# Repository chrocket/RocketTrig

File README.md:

# RocketTrig
A camera controller for photographing high poweed model rockets

This is a camera controller. Each "node" contains outputs to control one or two cameras.  Camera nodes can communicate to each others over an RF link. Two nodes make up a system, say one at the flight line and one up close to the rocket. Liftoffs can be triggered by a variety of sensors to detect lift-off, or manually via a foot switch.

Schematic, BOM, JLBPCB files and firmware are all included.
Note:  Even those some files are labelled "CameraTriggerSensorNodeOnly" they are really Camera nodes.

This is based on the Adafruit Feather M0 LoRa board (Adafruit 3178). It also works with RFM65 radio version of that board, cheaper but less range (Adafruit 3176). There is a #define to select between the two, and the frequency of operation will have to be in the range of the chip.

To build firmware, you will need Arduino IDE. I'm using ver 1.8.19.  You will need to set up the Adafruit boards in the boards manager (Add https://adafruit.github.io/arduino-board-index/package_adafruit_index.json to Additional boards URL under Preferences).  Set "Adafruit Feather M0 (SAMD21)" Under Tools/Board.

I'm using dependencies (under library manager):
CRC32 by Christopher Baker  https://github.com/bakercp/CRC32/blob/master/examples/CRC32/CRC32.ino
Requires RadioHead libs
// https://www.airspayce.com/mikem/arduino/RadioHead/index.html
// Download from Adafruit https://cdn-learn.adafruit.com/assets/assets/000/035/106/original/RadioHead-1.62.zip?1472068723
CCW MorseTX
https://github.com/ridencww/cww_MorseTx

You will likely want to change the default 915.35 MHz operating frequency. This is done by a #define.  This will deconfict different users who might want to simultaneously use the sytem.

--------------------------------------------------------------------------------------------------------------
In June 2023, I had Eureka moment. I realized that with virtuallly no changes, the RocketTrig board could be used as a wireless Launch controller and still trigger cameras.  I modified the program to work with this and later worked up a separate board "Rev 4_1" that could better meet both remote launch and remote camera trigger functions.

(Remote launch can still trigger cameras both local and remote)

Here is the Rev 4_1 board

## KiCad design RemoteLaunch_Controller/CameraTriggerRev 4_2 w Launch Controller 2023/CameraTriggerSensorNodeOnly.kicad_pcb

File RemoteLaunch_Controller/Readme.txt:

Uses the CameraTrig board, as-is to create a wireless launch capability.

(Some pins for sensors are needed for a relay and LED).

Camera will trigger when "launch" is fired (for a two second "on")

Poll button becomes "clear", "Arm" is still "Arm" and "Trigger" becomes launch.

Press "Arm", which will arm system, after 15 sec, it will time out.
- Will also go to disarm, if you hit "clear"
- Will disarm after a launch.

After system is in "arm", hit "launch" to fire the ignitors in the remote box for 2s
- Hitting "clear" will turn off ignitors, if still in the 2 s window

Schematics enclosed for external board connections, as well as BOM.

***********************************************
NOTE  Variations
***********************************************
RocketTrig_based_board  is based on the orinal board   6/2023

CameraTriggerRev 4_2 w Launch Controller 2023  is a re-do with i2c i/o expander and darlington driver array  7/2023
4ChWirelessLaunchController - try 2 w relay pcb - is a relay board for Rev 4_2  7/2023

***********************************************
NOTE  Migrated to Kicad 7
***********************************************

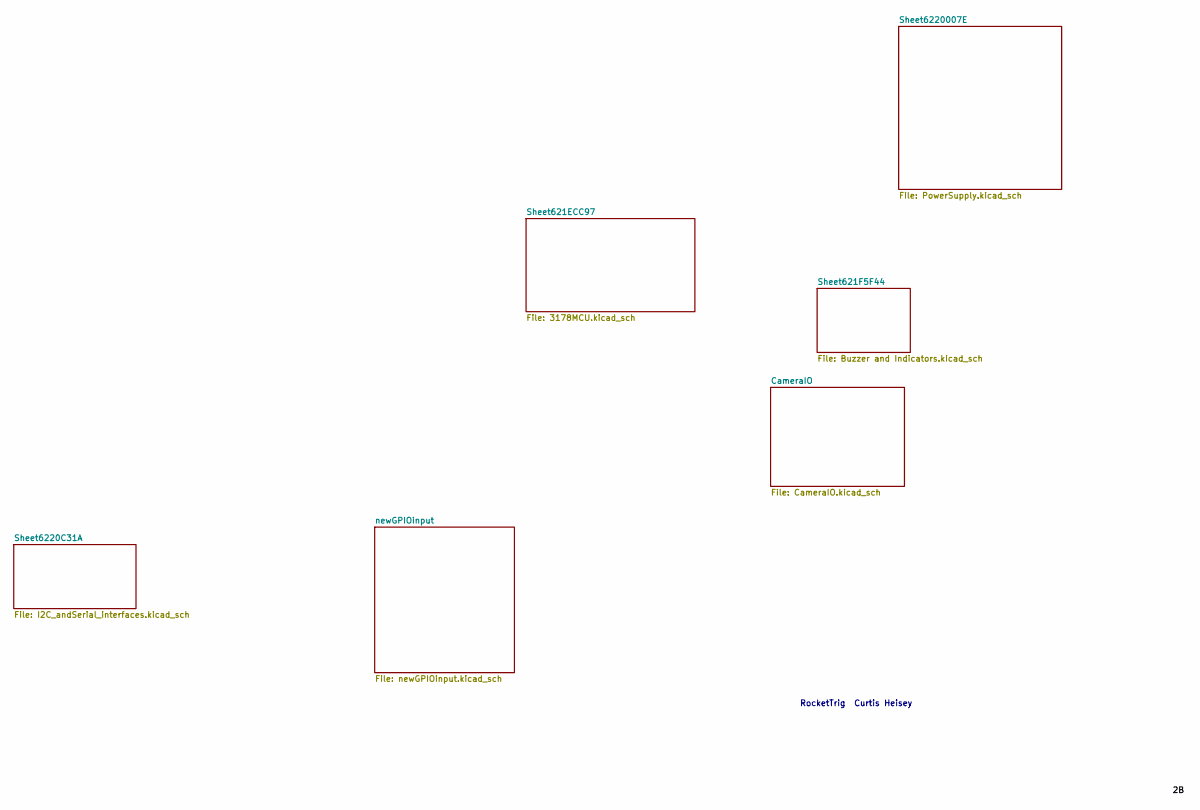
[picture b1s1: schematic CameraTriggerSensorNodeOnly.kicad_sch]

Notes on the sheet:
RocketTrig Curtis Heisey

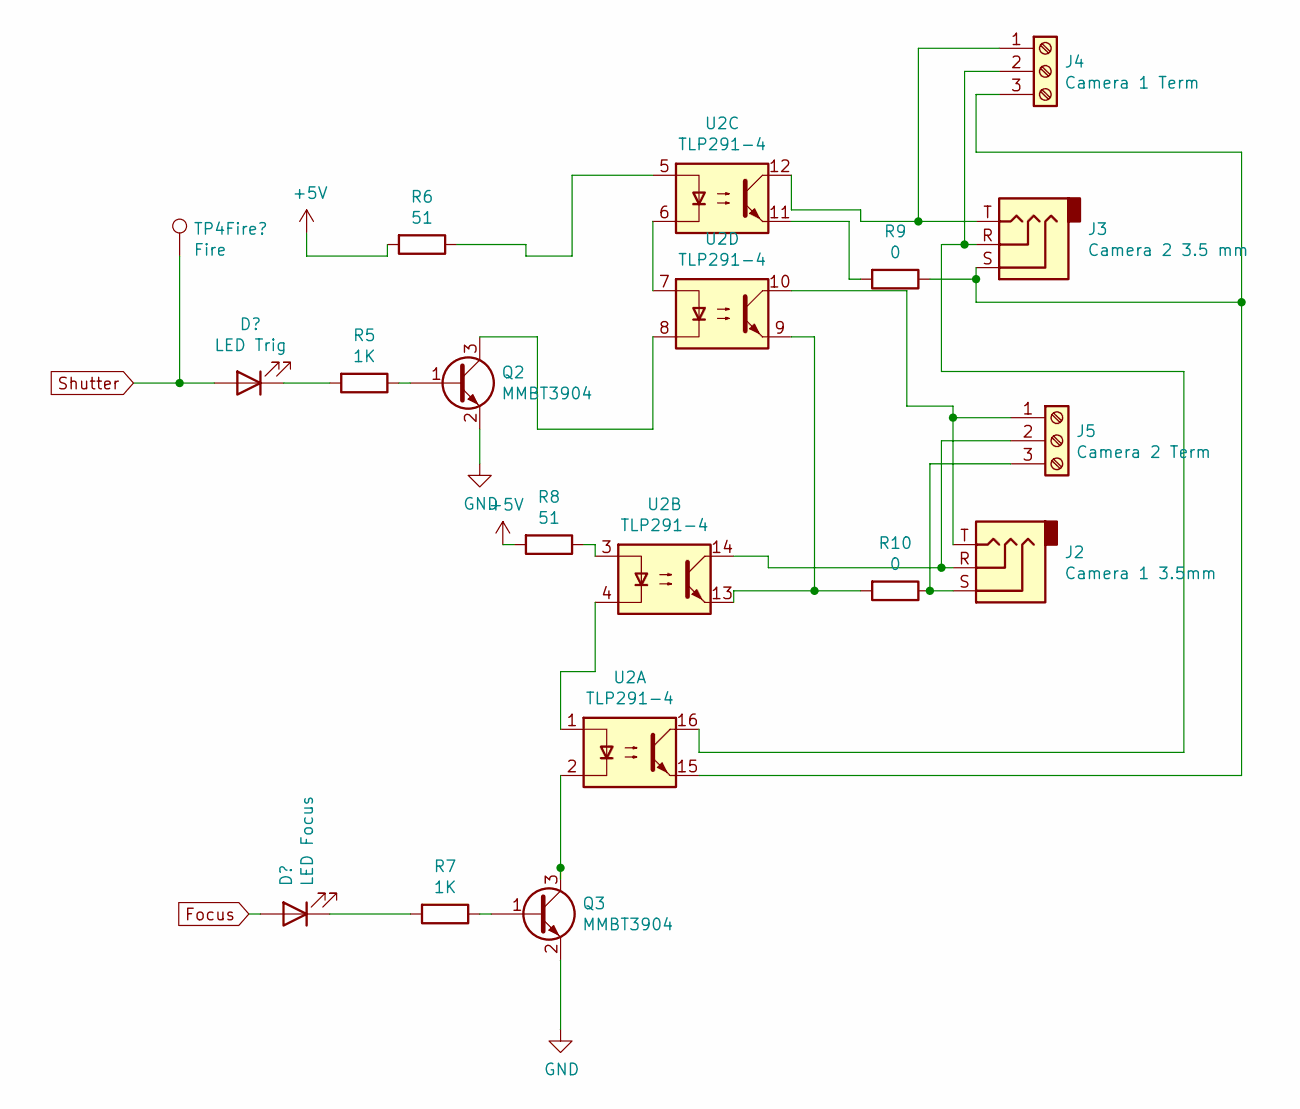
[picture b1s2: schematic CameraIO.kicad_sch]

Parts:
D4: LED Trig; LED_0805_2012Metric_Castellated
D5: LED Focus; LED_0805_2012Metric_Pad1.15x1.40mm_HandSolder
J2: Camera 1 3.5mm; Jack_3.5mm_CUI_SJ1-3533NG_Horizontal_CircularHoles
J3: Camera 2 3.5 mm; Jack_3.5mm_CUI_SJ1-3533NG_Horizontal_CircularHoles
J4: Camera 1 Term; TerminalBlock_TE_282834-3_1x03_P2.54mm_Horizontal
J5: Camera 2 Term; TerminalBlock_TE_282834-3_1x03_P2.54mm_Horizontal
Q2, Q3: MMBT3904; SOT-23; LCSC C8512
R5, R7: 1K; R_0603_1608Metric; LCSC C22843
R6, R8: 51; R_0603_1608Metric; LCSC C880145
R9, R10: 0; R_0805_2012Metric_Pad1.15x1.40mm_HandSolder; LCSC C17477
TP4Fire1: Fire; TestPoint_Keystone_5010-5014_Multipurpose
U2: TLP291-4; SOIC-16_4.55x10.3mm_P1.27mm; LCSC C60900

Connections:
+5V: R6.2, R8.2; also elsewhere on the board
Focus: D5.2 (A); also elsewhere on the board
GND: Q2.2 (E), Q3.2 (E); also elsewhere on the board
unnamed: D4.1 (K), R5.2
unnamed: D5.1 (K), R7.2
unnamed: J2.R, J5.2, U2.14
unnamed: J2.S, J5.3, R10.1
unnamed: J2.T, J5.1, U2.10
unnamed: J3.R, J4.2, U2.16
unnamed: J3.S, J4.3, R9.1, U2.15
unnamed: J3.T, J4.1, U2.12
unnamed: Q2.1 (B), R5.1
unnamed: Q2.3 (C), U2.8
unnamed: Q3.1 (B), R7.1
unnamed: Q3.3 (C), U2.2
unnamed: R6.1, U2.5
unnamed: R8.1, U2.3
unnamed: R9.2, U2.11
unnamed: R10.2, U2.9, U2.13
unnamed: U2.1, U2.4
unnamed: U2.6, U2.7
Shutter: D4.2 (A), TP4Fire1.1; also elsewhere on the board

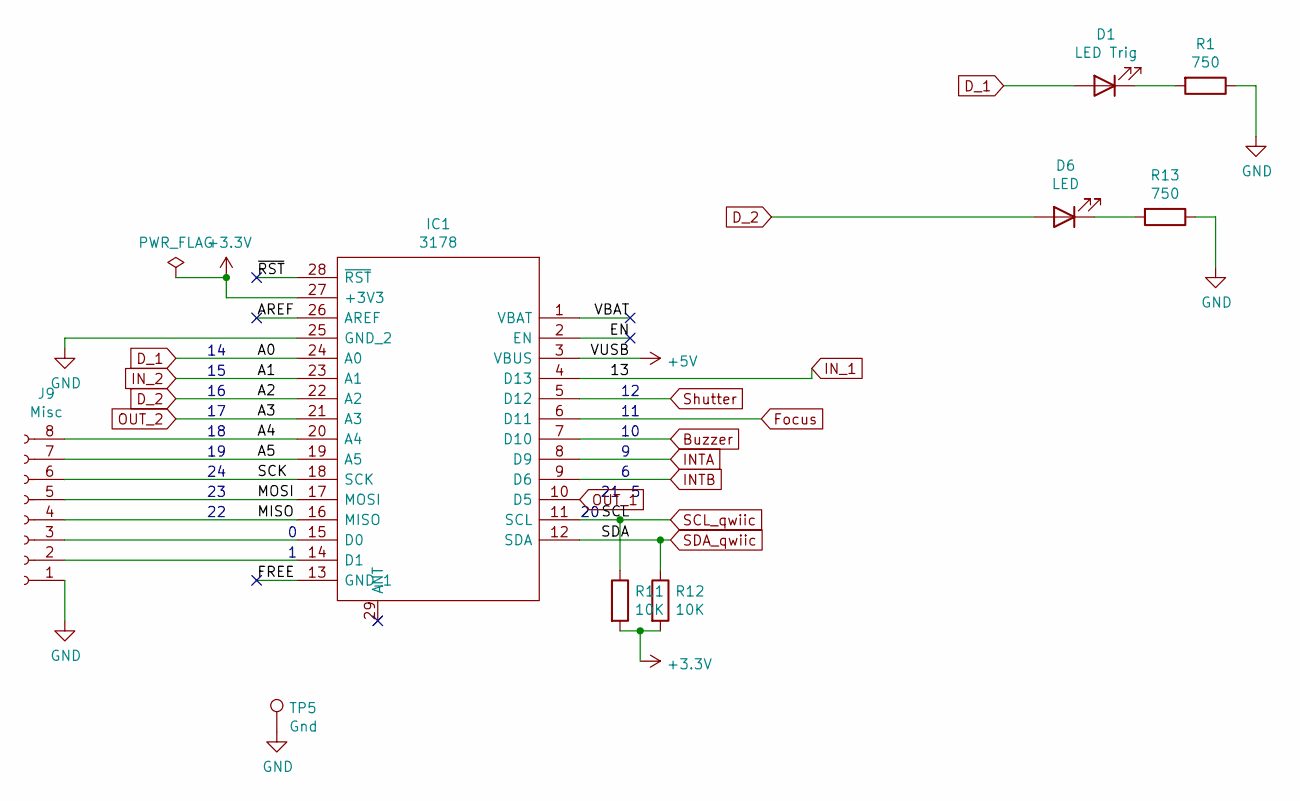
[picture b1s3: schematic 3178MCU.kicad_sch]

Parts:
D1: LED Trig; LED_0805_2012Metric_Pad1.15x1.40mm_HandSolder
D6: LED; LED_0805_2012Metric_Pad1.15x1.40mm_HandSolder
IC1: 3178; Mouser2 Part Number 485-3178
J9: Misc; PinHeader_1x08_P2.54mm_Vertical
R1, R13: 750; R_0603_1608Metric; LCSC C23241
R11, R12: 10K; R_0603_1608Metric; LCSC C25804
TP5: Gnd; TestPoint_Keystone_5000-5004_Miniature

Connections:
+3V3: IC1.27 (+3V3), R11.2, R12.2; also elsewhere on the board
+5V: IC1.3 (VBUS); also elsewhere on the board
/Sheet621ECC97/A4: IC1.20 (A4), J9.8
/Sheet621ECC97/A5: IC1.19 (A5), J9.7
/Sheet621ECC97/AREF: IC1.26 (AREF)
/Sheet621ECC97/EN: IC1.2 (EN)
/Sheet621ECC97/FREE: IC1.13 (GND_1)
/Sheet621ECC97/MISO: IC1.16 (MISO), J9.4
/Sheet621ECC97/MOSI: IC1.17 (MOSI), J9.5
/Sheet621ECC97/SCK: IC1.18 (SCK), J9.6
/Sheet621ECC97/VBAT: IC1.1 (VBAT)
/Sheet621ECC97/~RST: IC1.28 (~RST)
Buzzer: IC1.7 (D10); also elsewhere on the board
D_1: D1.2 (A), IC1.24 (A0)
D_2: D6.2 (A), IC1.22 (A2)
Focus: IC1.6 (D11); also elsewhere on the board
GND: IC1.25 (GND_2), J9.1, R1.1, R13.1, TP5.1; also elsewhere on the board
INTA: IC1.8 (D9); also elsewhere on the board
INTB: IC1.9 (D6); also elsewhere on the board
IN_1: IC1.4 (D13); also elsewhere on the board
IN_2: IC1.23 (A1); also elsewhere on the board
unnamed: D1.1 (K), R1.2
unnamed: D6.1 (K), R13.2
unnamed: IC1.14 (D1), J9.2
unnamed: IC1.15 (D0), J9.3
OUT_1: IC1.10 (D5); also elsewhere on the board
OUT_2: IC1.21 (A3); also elsewhere on the board
SCL_qwiic: IC1.11 (SCL), R11.1; also elsewhere on the board
SDA_qwiic: IC1.12 (SDA), R12.1; also elsewhere on the board
Shutter: IC1.5 (D12); also elsewhere on the board

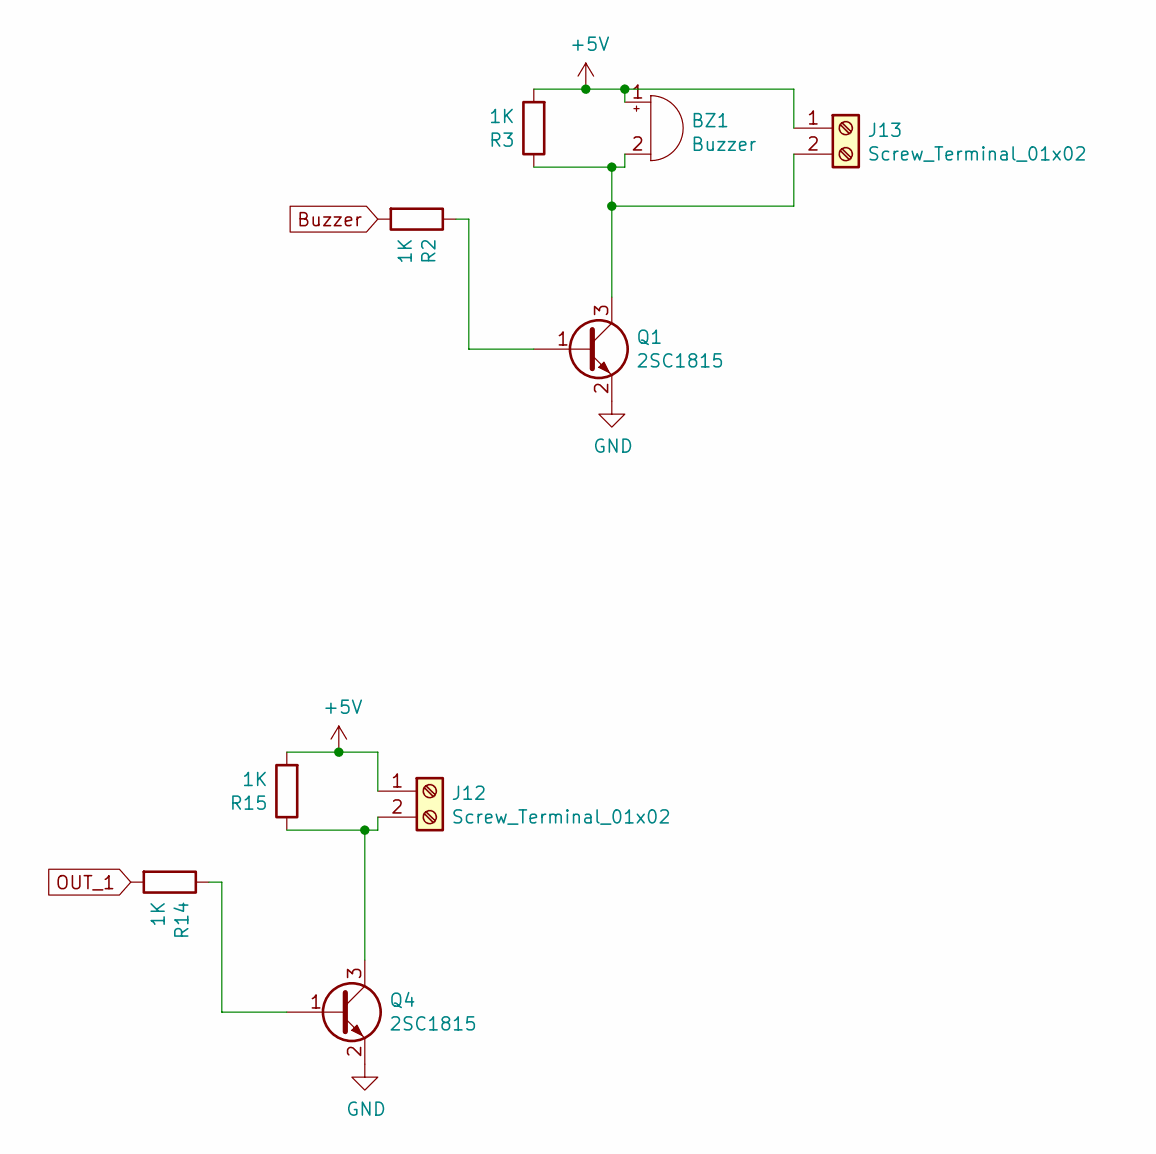
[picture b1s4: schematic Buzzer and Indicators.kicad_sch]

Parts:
BZ1: Buzzer; Buzzer_TDK_PS1240P02BT_D12.2mm_H6.5mm
J12, J13: Screw_Terminal_01x02; TerminalBlock_TE_282834-2_1x02_P2.54mm_Horizontal
Q1, Q4: 2SC1815; SOT-23; LCSC C181171
R2, R3, R14, R15: 1K; R_0603_1608Metric; LCSC C21190

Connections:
+5V: BZ1.1 (-), J12.1, J13.1, R3.2, R15.2; also elsewhere on the board
Buzzer: R2.2; also elsewhere on the board
GND: Q1.2 (E), Q4.2 (E); also elsewhere on the board
unnamed: BZ1.2 (+), J13.2, Q1.3 (C), R3.1
unnamed: J12.2, Q4.3 (C), R15.1
unnamed: Q1.1 (B), R2.1
unnamed: Q4.1 (B), R14.1
OUT_1: R14.2; also elsewhere on the board

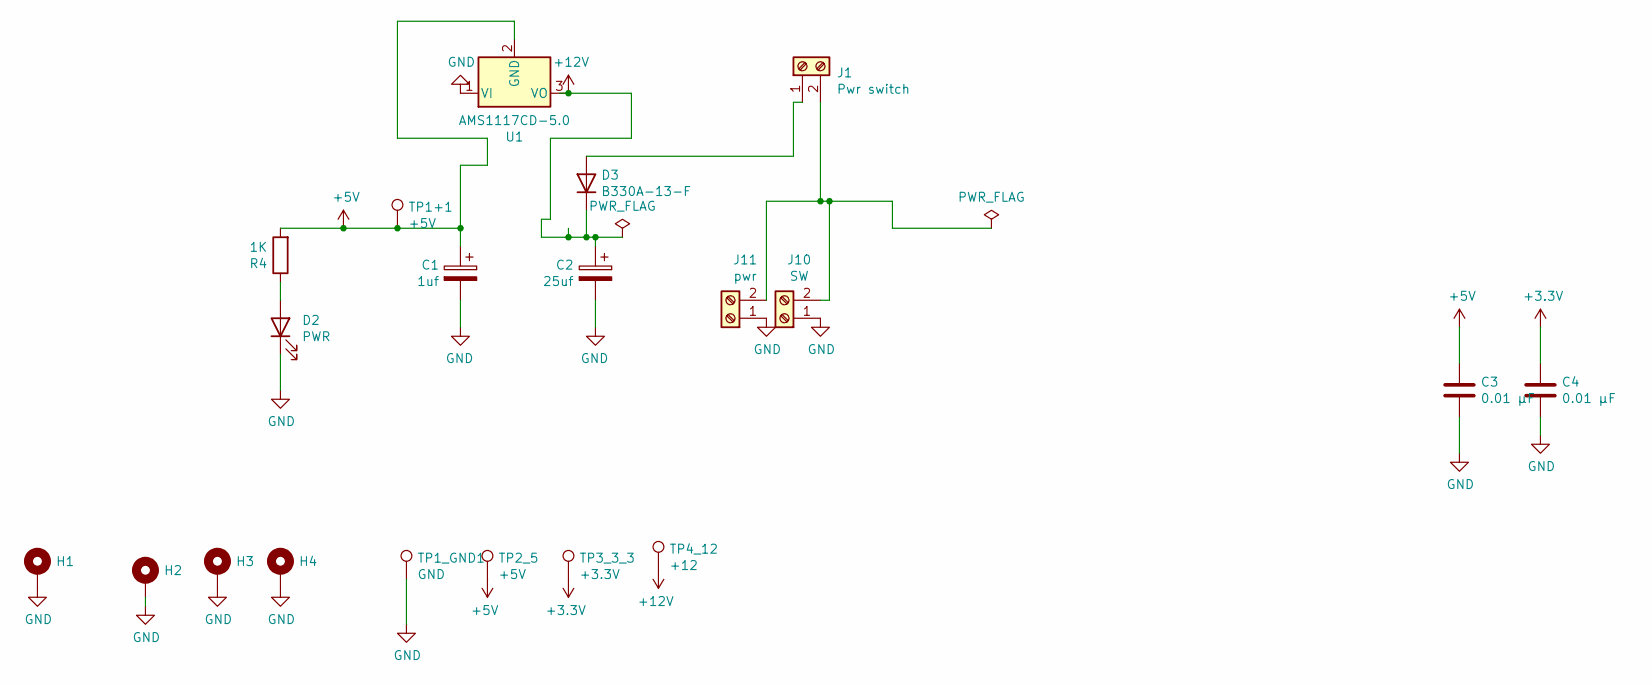
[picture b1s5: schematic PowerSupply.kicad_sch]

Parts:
C1: 1uf; CP_Elec_4x5.4; LCSC C87863
C2: 25uf; C_Elec_4x5.4; LCSC C2895283
C3, C4: 0.01 μF; C_0402_1005Metric; LCSC C1525
D2: PWR; LED_0603_1608Metric; LCSC C2286
D3: B330A-13-F; D_SMA; LCSC C110485
H1, H2, H3, H4: MountingHole_3.7mm_Pad
J1: Pwr switch; CUI_TB007-508-02BE
J10: SW; AMASS_XT30U-F_1x02_P5.0mm_Vertical
J11: pwr; CUI_TB007-508-02BE
R4: 1K; R_0603_1608Metric; LCSC C21190
TP1+1, TP2_5: +5V; TestPoint_Keystone_5010-5014_Multipurpose
TP1_GND1: GND; TestPoint_Keystone_5010-5014_Multipurpose
TP3_3_3: +3.3V; TestPoint_Keystone_5010-5014_Multipurpose
TP4_12: +12; TestPoint_Keystone_5010-5014_Multipurpose
U1: AMS1117CD-5.0; SOT-223; LCSC C6187

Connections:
+3V3: C4.1, TP3_3_3.1; also elsewhere on the board
+5V: C1.1, C3.1, R4.2, TP1+1.1, TP2_5.1, U1.2 (GND); also elsewhere on the board
+12V: C2.1, D3.1 (K), TP4_12.1, U1.3 (VO); also elsewhere on the board
GND: C1.2, C2.2, C3.2, C4.2, D2.1 (K), H1.1, H2.1, H3.1, H4.1, J10.1, J11.1, TP1_GND1.1, U1.1 (VI); also elsewhere on the board
unnamed: D2.2 (A), R4.1
unnamed: D3.2 (A), J1.1
unnamed: J1.2, J10.2, J11.2

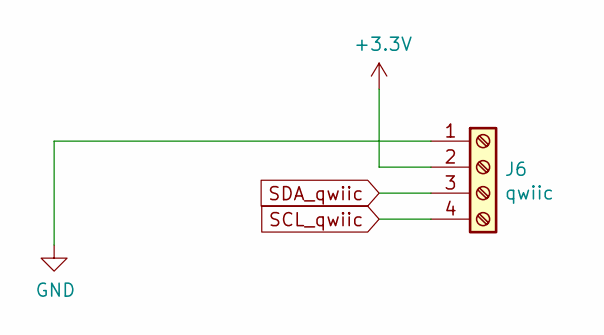
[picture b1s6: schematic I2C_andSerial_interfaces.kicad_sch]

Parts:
J6: qwiic; JST_SH_SM04B-SRSS-TB_1x04-1MP_P1.00mm_Horizontal; LCSC C160404

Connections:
+3V3: J6.2; also elsewhere on the board
GND: J6.1; also elsewhere on the board
SCL_qwiic: J6.4; also elsewhere on the board
SDA_qwiic: J6.3; also elsewhere on the board

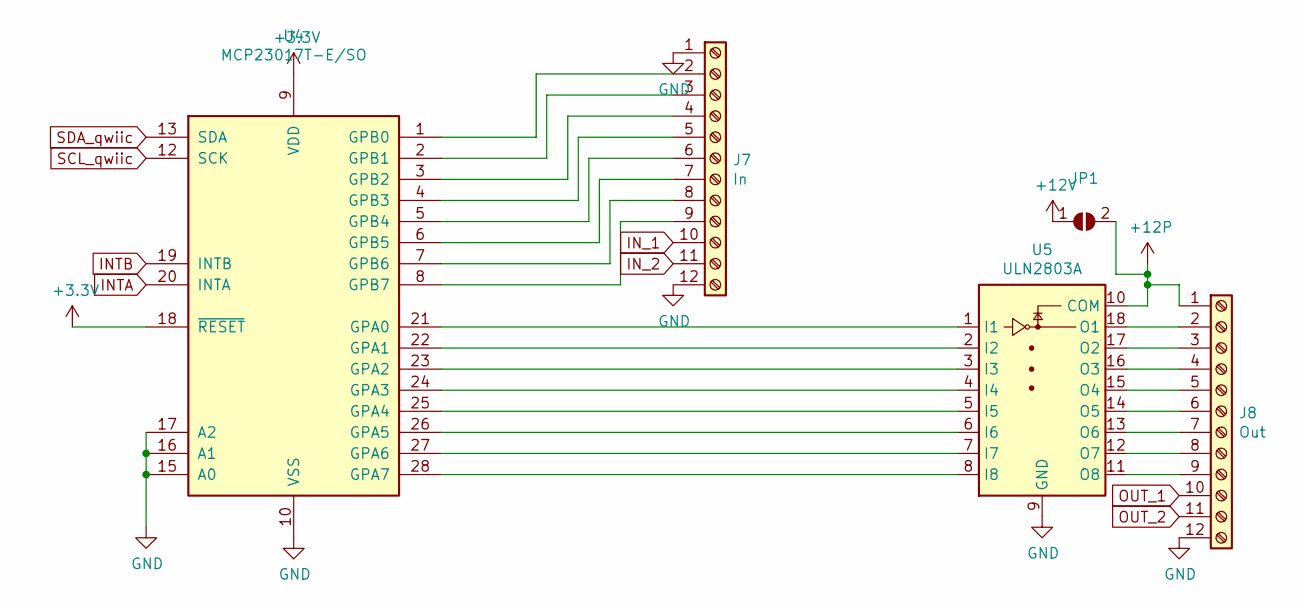
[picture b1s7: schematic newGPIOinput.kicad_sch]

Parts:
J7: In; TB00750812BE
J8: Out; TB00750812BE
JP1: SolderJumper-2_P1.3mm_Open_TrianglePad1.0x1.5mm
U4: MCP23017T-E/SO; SOIC-28W_7.5x17.9mm_P1.27mm; LCSC C629440
U5: ULN2803A; SOIC127P1030X265-18N; LCSC C9683

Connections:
+3V3: U4.9 (VDD), U4.18 (~RESET); also elsewhere on the board
+12P: J8.1, JP1.2 (B), U5.10 (COM)
+12V: JP1.1 (A); also elsewhere on the board
GND: J7.1, J7.12, J8.12, U4.10 (VSS), U4.15 (A0), U4.16 (A1), U4.17 (A2), U5.9 (GND); also elsewhere on the board
INTA: U4.20 (INTA); also elsewhere on the board
INTB: U4.19 (INTB); also elsewhere on the board
IN_1: J7.10; also elsewhere on the board
IN_2: J7.11; also elsewhere on the board
unnamed: J7.2, U4.1 (GPB0)
unnamed: J7.3, U4.2 (GPB1)
unnamed: J7.4, U4.3 (GPB2)
unnamed: J7.5, U4.4 (GPB3)
unnamed: J7.6, U4.5 (GPB4)
unnamed: J7.7, U4.6 (GPB5)
unnamed: J7.8, U4.7 (GPB6)
unnamed: J7.9, U4.8 (GPB7)
unnamed: J8.2, U5.18 (O1)
unnamed: J8.3, U5.17 (O2)
unnamed: J8.4, U5.16 (O3)
unnamed: J8.5, U5.15 (O4)
unnamed: J8.6, U5.14 (O5)
unnamed: J8.7, U5.13 (O6)
unnamed: J8.8, U5.12 (O7)
unnamed: J8.9, U5.11 (O8)
unnamed: U4.21 (GPA0), U5.1 (I1)
unnamed: U4.22 (GPA1), U5.2 (I2)
unnamed: U4.23 (GPA2), U5.3 (I3)
unnamed: U4.24 (GPA3), U5.4 (I4)
unnamed: U4.25 (GPA4), U5.5 (I5)
unnamed: U4.26 (GPA5), U5.6 (I6)
unnamed: U4.27 (GPA6), U5.7 (I7)
unnamed: U4.28 (GPA7), U5.8 (I8)
OUT_1: J8.10; also elsewhere on the board
OUT_2: J8.11; also elsewhere on the board
SCL_qwiic: U4.12 (SCK); also elsewhere on the board
SDA_qwiic: U4.13 (SDA); also elsewhere on the board

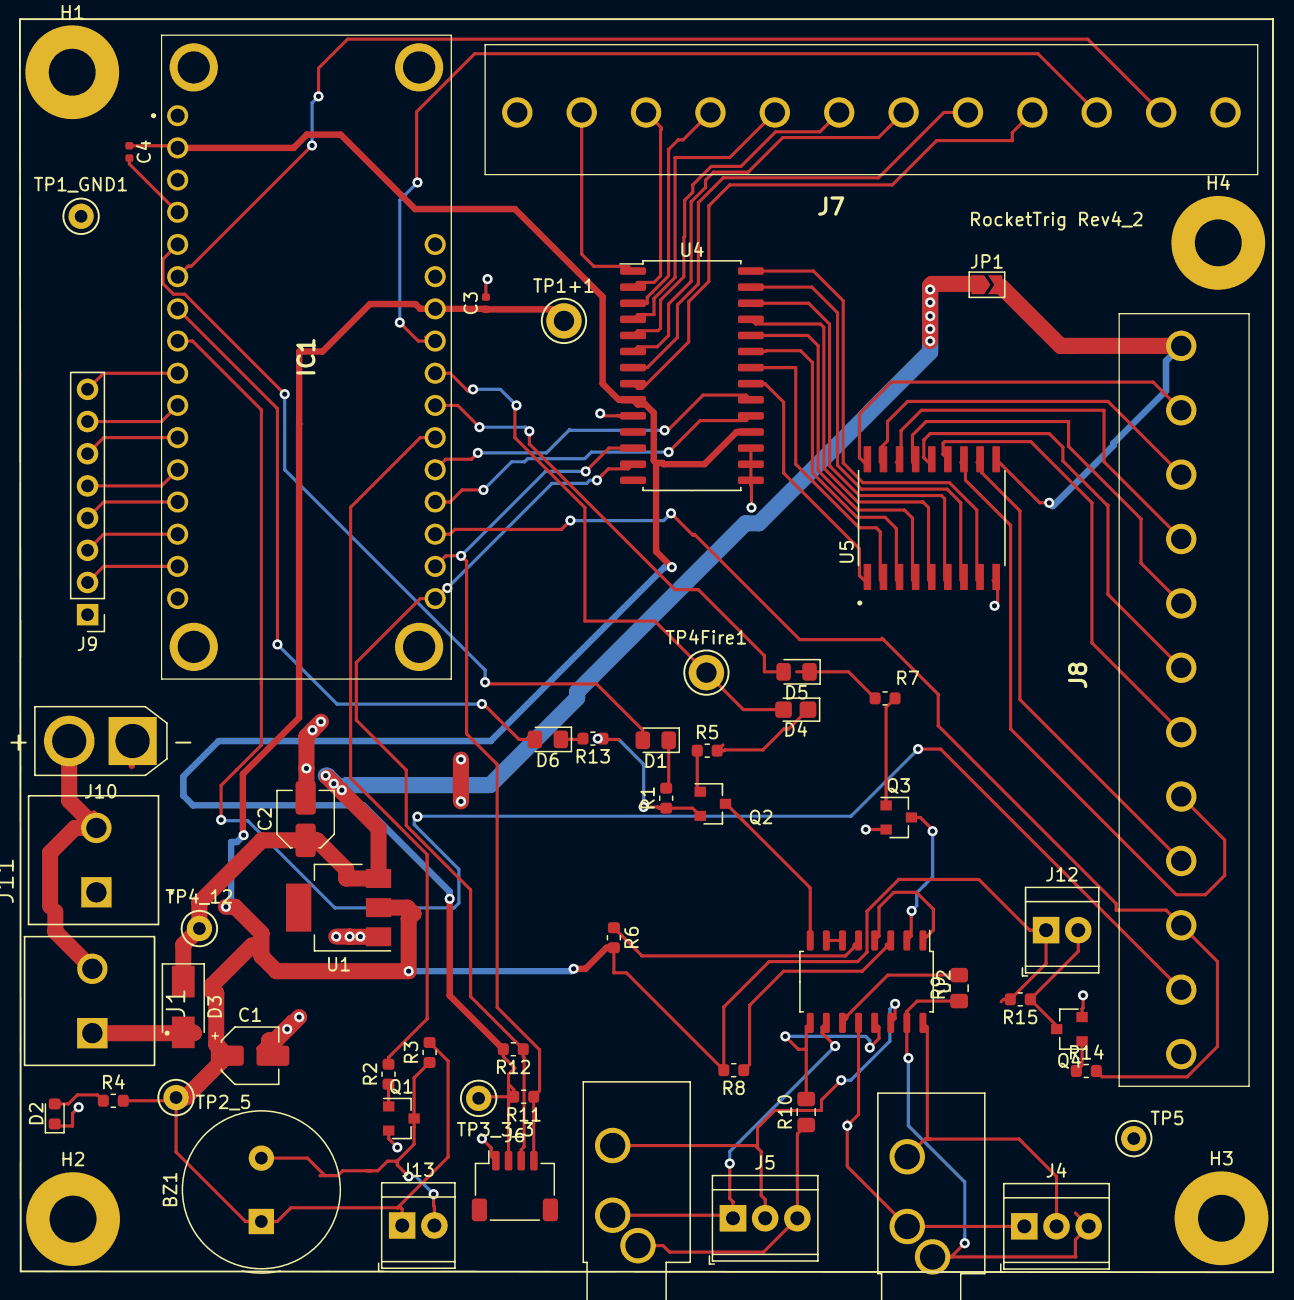
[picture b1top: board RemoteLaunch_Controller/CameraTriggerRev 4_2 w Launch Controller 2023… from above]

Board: 2 copper layers, 60 parts (0 on the bottom side), 76 nets.

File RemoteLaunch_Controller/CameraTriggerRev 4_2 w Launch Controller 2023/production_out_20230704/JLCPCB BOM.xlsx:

Comment | Designator | Footprint | LCSC
0 | R9,R10 | Resistor_SMD:R_0805_2012Metric_Pad1.15x1.40mm_HandSolder | C17477
2SC1815 | Q1,Q4 | Package_TO_SOT_SMD:SOT-23 | C181171
25uf | C2 | Capacitor_SMD:C_Elec_4x5.4 | C2895283
TLP291-4 | U2 | Package_SO:SOIC-16_4.55x10.3mm_P1.27mm | C60900
51 | R6,R8 | Resistor_SMD:R_0603_1608Metric | C880145
B330A-13-F | D3 | Diode_SMD:D_SMA | C110485
0.01 μF | C3,C4 | Capacitor_SMD:C_0402_1005Metric | C1525
qwiic | J6 | Connector_JST:JST_SH_SM04B-SRSS-TB_1x04-1MP_P1.00mm_Horizontal | C160404
1K | R2,R3,R4,R5,R7,R14,R15 | Resistor_SMD:R_0603_1608Metric | C21190
PWR | D2 | LED_SMD:LED_0603_1608Metric | C2286
750 | R1,R13 | Resistor_SMD:R_0603_1608Metric | C23241
10K | R11,R12 | Resistor_SMD:R_0603_1608Metric | C25804
AMS1117CD-5.0 | U1 | Package_TO_SOT_SMD:SOT-223 | C6187
MCP23017T-E/SO | U4 | Package_SO:SOIC-28W_7.5x17.9mm_P1.27mm | C629440
MMBT3904 | Q2,Q3 | Package_TO_SOT_SMD:SOT-23 | C8512
1uf | C1 | Capacitor_SMD:CP_Elec_4x5.4 | C87863
ULN2803A | U5 | CameraTriggerPCB:SOIC127P1030X265-18N | C9683
Buzzer | BZ1 | Buzzer_Beeper:Buzzer_TDK_PS1240P02BT_D12.2mm_H6.5mm
LED Trig | D1 | LED_SMD:LED_0805_2012Metric_Pad1.15x1.40mm_HandSolder
LED Trig | D4 | LED_SMD:LED_0805_2012Metric_Castellated
LED Focus | D5 | LED_SMD:LED_0805_2012Metric_Pad1.15x1.40mm_HandSolder
LED | D6 | LED_SMD:LED_0805_2012Metric_Pad1.15x1.40mm_HandSolder
 | H1,H2,H3,H4 | MountingHole:MountingHole_3.7mm_Pad
3178 | IC1 | 3178
Pwr switch | J1 | CameraTriggerPCB:CUI_TB007-508-02BE
SW | J10 | Connector_AMASS:AMASS_XT30U-F_1x02_P5.0mm_Vertical
pwr | J11 | CameraTriggerPCB:CUI_TB007-508-02BE
Screw_Terminal_01x02 | J12,J13 | TerminalBlock_TE-Connectivity:TerminalBlock_TE_282834-2_1x02_P2.54mm_Horizontal
Camera 1 3.5mm | J2 | Connector_Audio:Jack_3.5mm_CUI_SJ1-3533NG_Horizontal_CircularHoles
Camera 2 3.5 mm | J3 | Connector_Audio:Jack_3.5mm_CUI_SJ1-3533NG_Horizontal_CircularHoles
Camera 1 Term | J4 | TerminalBlock_TE-Connectivity:TerminalBlock_TE_282834-3_1x03_P2.54mm_Horizontal
Camera 2 Term | J5 | TerminalBlock_TE-Connectivity:TerminalBlock_TE_282834-3_1x03_P2.54mm_Horizontal
In | J7 | CameraTriggerPCB:TB00750812BE
Out | J8 | CameraTriggerPCB:TB00750812BE
Misc | J9 | Connector_PinHeader_2.54mm:PinHeader_1x08_P2.54mm_Vertical
 | JP1 | Jumper:SolderJumper-2_P1.3mm_Open_TrianglePad1.0x1.5mm
+5V | TP1+1,TP2_5 | TestPoint:TestPoint_Keystone_5010-5014_Multipurpose
GND | TP1_GND1 | TestPoint:TestPoint_Keystone_5010-5014_Multipurpose
+3.3V | TP3_3_3 | TestPoint:TestPoint_Keystone_5010-5014_Multipurpose
Fire | TP4Fire1 | TestPoint:TestPoint_Keystone_5010-5014_Multipurpose
12 | TP4_12 | TestPoint:TestPoint_Keystone_5010-5014_Multipurpose
Gnd | TP5 | TestPoint:TestPoint_Keystone_5000-5004_Miniature

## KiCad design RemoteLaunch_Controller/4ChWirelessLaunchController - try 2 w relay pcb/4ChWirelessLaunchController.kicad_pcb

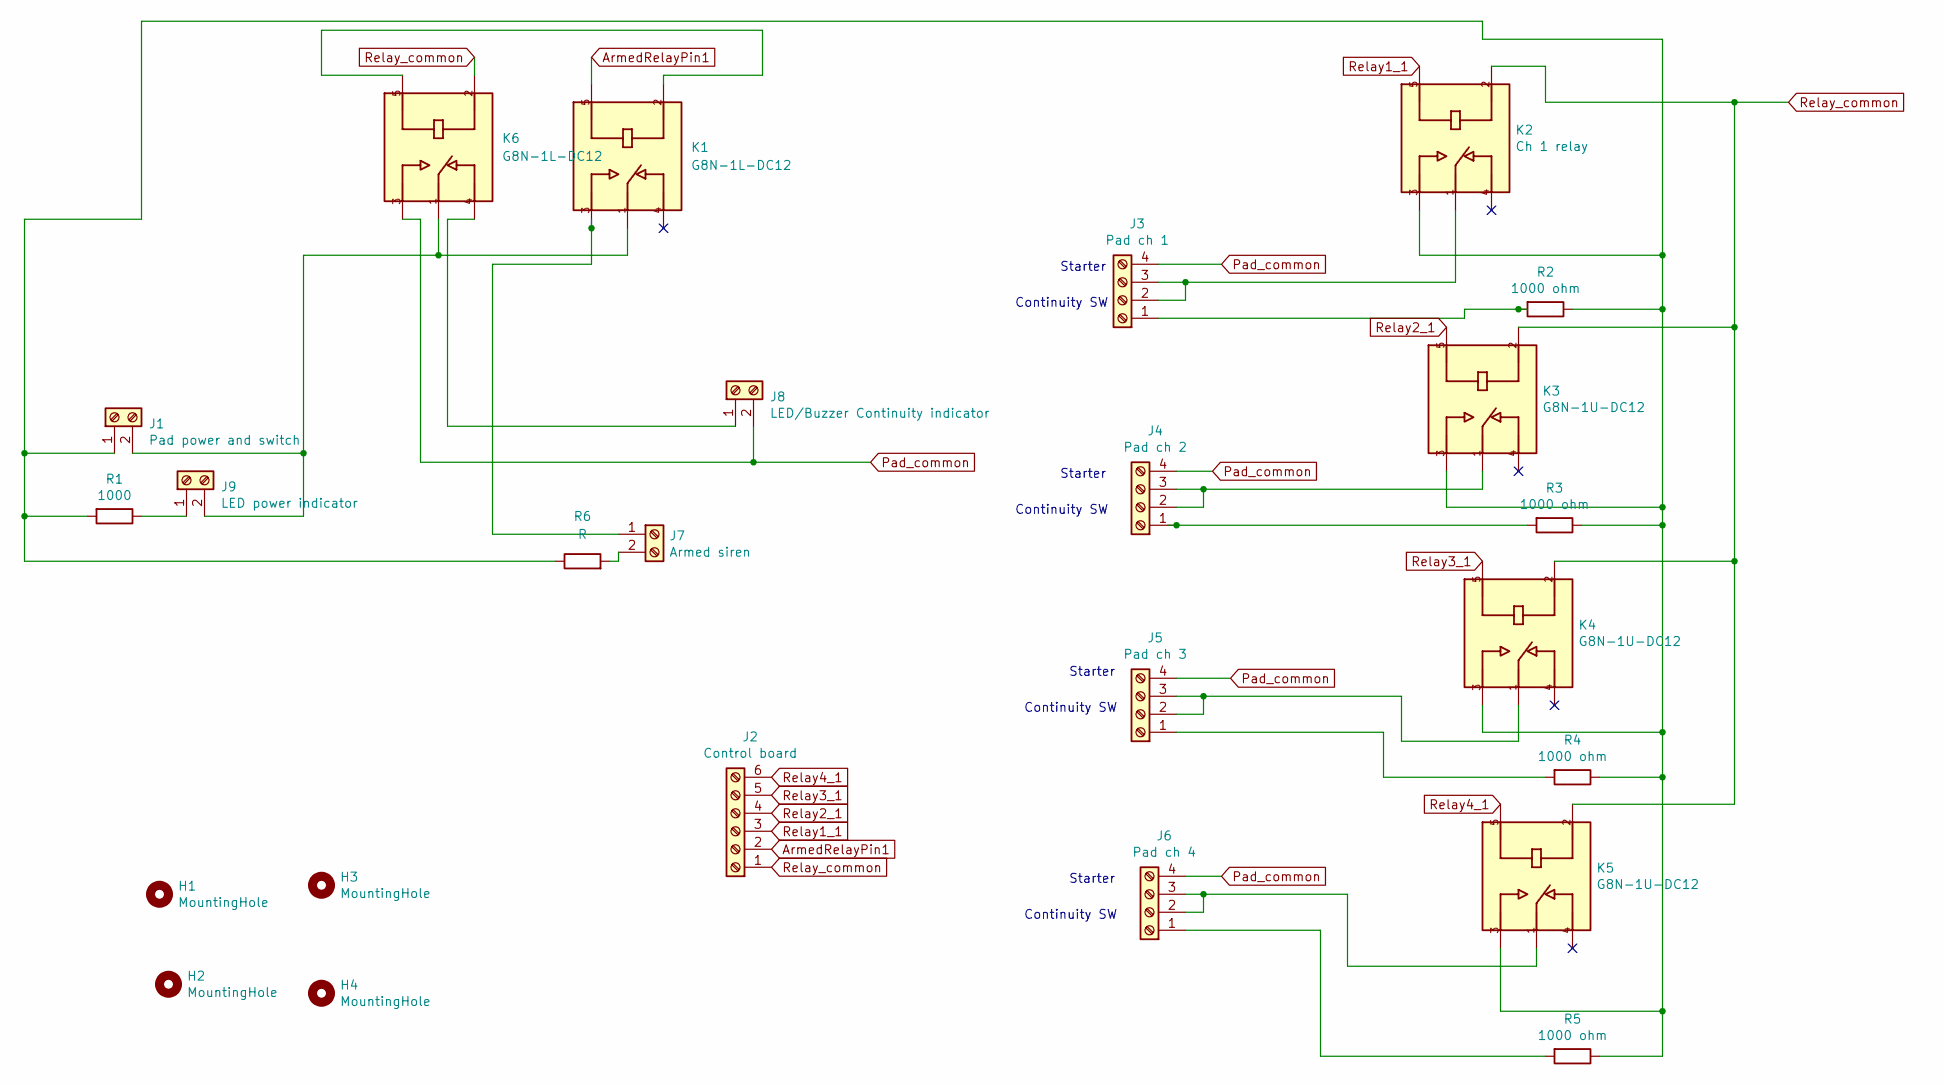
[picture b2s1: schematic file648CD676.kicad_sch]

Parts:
H1, H2, H3, H4: MountingHole; MountingHole_5.3mm_M5_DIN965_Pad
J1: Pad power and switch; CUI_TB007-508-02BE
J2: Control board; CUI_TB007-508-06BE
J3: Pad ch 1; CUI_TB007-508-04BE
J4: Pad ch 2; CUI_TB007-508-04BE
J5: Pad ch 3; CUI_TB007-508-04BE
J6: Pad ch 4; CUI_TB007-508-04BE
J7: Armed siren; CUI_TB007-508-02BE
J8: LED/Buzzer Continuity indicator; CUI_TB007-508-02BE
J9: LED power indicator; CUI_TB007-508-02BE
K1, K6: G8N-1L-DC12; RELAY_G8N-1U-DC12; PARTREV NA
K2: Ch 1 relay; RELAY_G8N-1U-DC12; PARTREV NA
K3, K4, K5: G8N-1U-DC12; RELAY_G8N-1U-DC12; PARTREV NA
R1: 1000; R_Axial_DIN0207_L6.3mm_D2.5mm_P7.62mm_Horizontal
R2, R3, R4, R5: 1000 ohm; R_Axial_DIN0207_L6.3mm_D2.5mm_P7.62mm_Horizontal
R6: R; R_Axial_DIN0207_L6.3mm_D2.5mm_P7.62mm_Horizontal

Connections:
ArmedRelayPin1: J2.2, K1.5
unnamed: J1.1, K2.3, K3.3, K4.3, K5.3, R1.2, R2.1, R3.1, R4.1, R5.1, R6.1
unnamed: J1.2, J9.2, K1.1, K6.1
unnamed: J3.1, R2.2
unnamed: J3.2, J3.3, K2.1
unnamed: J4.1, R3.2
unnamed: J4.2, J4.3, K3.1
unnamed: J5.1, R4.2
unnamed: J5.2, J5.3, K4.1
unnamed: J6.1, R5.2
unnamed: J6.2, J6.3, K5.1
unnamed: J7.1, K1.3
unnamed: J7.2, R6.2
unnamed: J8.1, K6.4
unnamed: J9.1, R1.1
unnamed: K1.2, K6.5
Pad_common: J3.4, J4.4, J5.4, J6.4, J8.2, K6.3
Relay1_1: J2.3, K2.5
Relay2_1: J2.4, K3.5
Relay3_1: J2.5, K4.5
Relay4_1: J2.6, K5.5
Relay_common: J2.1, K2.2, K3.2, K4.2, K5.2, K6.2

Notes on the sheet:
Continuity SW
Starter

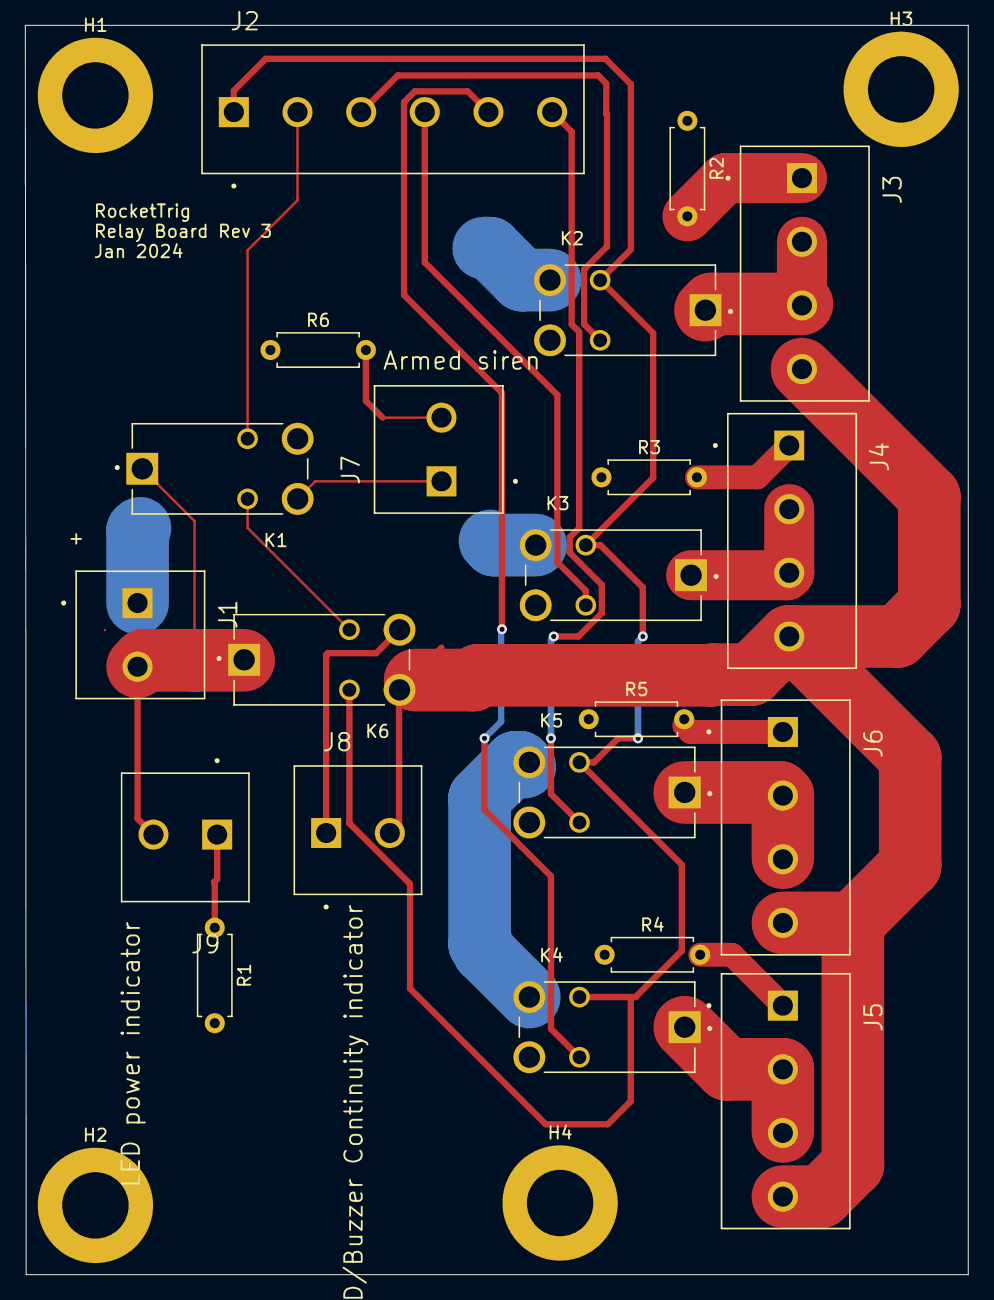
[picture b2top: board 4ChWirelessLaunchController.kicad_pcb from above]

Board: 2 copper layers, 75.2 x 99.7 mm, 25 parts (0 on the bottom side), 22 nets.

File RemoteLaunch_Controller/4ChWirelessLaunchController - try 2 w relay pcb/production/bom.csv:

Designator,Footprint,Quantity,Value,LCSC Part #
"H1, H2, H3, H4",MountingHole_5.3mm_M5_DIN965_Pad,4,MountingHole,
J1,CUI_TB007-508-02BE,1,Pad power and switch,
J2,CUI_TB007-508-06BE,1,Control board,
J3,CUI_TB007-508-04BE,1,Pad ch 1,
J4,CUI_TB007-508-04BE,1,Pad ch 2,
J5,CUI_TB007-508-04BE,1,Pad ch 3,
J6,CUI_TB007-508-04BE,1,Pad ch 4,
J7,CUI_TB007-508-02BE,1,Armed siren,
J8,CUI_TB007-508-02BE,1,LED/Buzzer Continuity indicator,
J9,CUI_TB007-508-02BE,1,LED power indicator,
"K1, K3, K4, K5",RELAY_G8N-1U-DC12,4,G8N-1U-DC12,
K2,RELAY_G8N-1U-DC12,1,Ch 1 relay,
R1,R_Axial_DIN0207_L6.3mm_D2.5mm_P7.62mm_Horizontal,1,1000,
"R2, R3, R4, R5",R_Axial_DIN0207_L6.3mm_D2.5mm_P7.62mm_Horizontal,4,1000 ohm,
R6,R_Axial_DIN0207_L6.3mm_D2.5mm_P7.62mm_Horizontal,1,R,
